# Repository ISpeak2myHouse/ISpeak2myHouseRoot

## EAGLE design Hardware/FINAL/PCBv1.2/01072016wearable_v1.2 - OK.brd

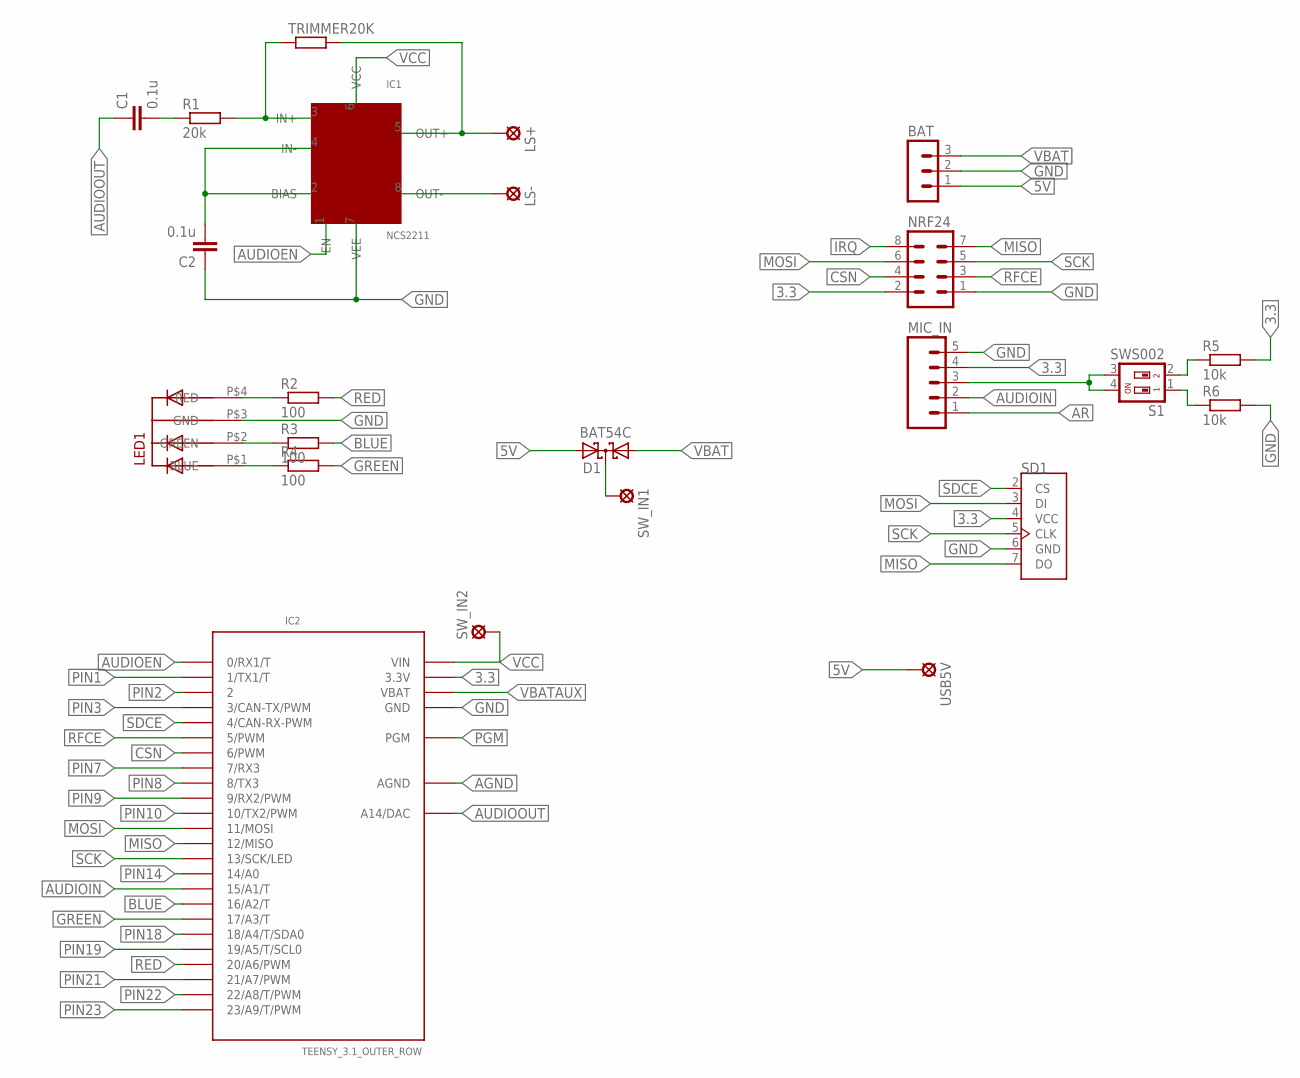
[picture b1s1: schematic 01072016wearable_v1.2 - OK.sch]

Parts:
BAT: MA03-1
C1, C2: 0.1u; C2.5-2
D1: BAT54C; SOT23
IC1: NCS2211; SOIC-8
IC2: TEENSY_3.1_OUTER_ROW; TEENSY3-OUTER_ROW
LED1: 5MMRGBLED; LED5MMRGB
LS+: LSP10
LS-: LSP10
MIC_IN: MA05; 05PA
NRF24: MA04-2
R1: 20k; 0204/7
R2, R3, R4: 100; 0207/2V
R5, R6: 10k; 0207/2V
S1: SWS002; SMS-002
SD1: MICROSD_SF-MICROSD; MICROSD_MICROSD
SW_IN1, SW_IN2: SE11
TRIMMER20K: R-EU_0207/2V; 0207/2V
USB5V: LSP10

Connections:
3.3: IC2.3.3V, IC2.3.3V1 (3.3V), MIC_IN.4, NRF24.2, R5.2, SD1.4 (VCC)
5V: BAT.1, D1.2 (A2), USB5V.MP
AGND: IC2.AGND
AR: MIC_IN.1
AUDIOEN: IC1.1 (EN), IC2.0 (0/RX1/T)
AUDIOIN: IC2.15/A1 (15/A1/T), MIC_IN.2
AUDIOOUT: C1.1, IC2.RESET/DAC (A14/DAC)
BLUE: IC2.16/A2 (16/A2/T), R3.2
CSN: IC2.6 (6/PWM), NRF24.4
GAIN: MIC_IN.3, S1.3, S1.4
GND: BAT.2, C2.1, IC1.7 (VEE), IC2.GND, IC2.GND1 (GND), LED1.P$3 (GND), MIC_IN.5, NRF24.1, R6.2, SD1.6 (GND)
GREEN: IC2.17/A3 (17/A3/T), R4.2
IRQ: NRF24.8
MISO: IC2.12 (12/MISO), NRF24.7, SD1.7 (DO)
MOSI: IC2.11 (11/MOSI), NRF24.6, SD1.3 (DI)
unnamed: D1.3 (CC), SW_IN1.MP
unnamed: IC1.5 (OUT+), LS+.MP, TRIMMER20K.2
unnamed: IC1.3 (IN+), R1.2, TRIMMER20K.1
unnamed: C1.2, R1.1
unnamed: C2.2, IC1.2 (BIAS), IC1.4 (IN-)
unnamed: IC1.8 (OUT-), LS-.MP
unnamed: LED1.P$4 (RED), R2.1
unnamed: LED1.P$1 (BLUE), R4.1
unnamed: LED1.P$2 (GREEN), R3.1
unnamed: R5.1, S1.2
unnamed: R6.1, S1.1
PGM: IC2.PGM
PIN1: IC2.1 (1/TX1/T)
PIN2: IC2.2
PIN3: IC2.3 (3/CAN-TX/PWM)
PIN7: IC2.7 (7/RX3)
PIN8: IC2.8 (8/TX3)
PIN9: IC2.9 (9/RX2/PWM)
PIN10: IC2.10 (10/TX2/PWM)
PIN14: IC2.14/A0
PIN18: IC2.18/A4 (18/A4/T/SDA0)
PIN19: IC2.19/A5 (19/A5/T/SCL0)
PIN21: IC2.21/A7 (21/A7/PWM)
PIN22: IC2.22/A8 (22/A8/T/PWM)
PIN23: IC2.23/A9 (23/A9/T/PWM)
RED: IC2.20/A6 (20/A6/PWM), R2.2
RFCE: IC2.5 (5/PWM), NRF24.3
SCK: IC2.13 (13/SCK/LED), NRF24.5, SD1.5 (CLK)
SDCE: IC2.4 (4/CAN-RX-PWM), SD1.2 (CS)
VBAT: BAT.3, D1.1 (A1)
VBATAUX: IC2.VBAT
VCC: IC1.6 (VCC), IC2.VIN, SW_IN2.MP

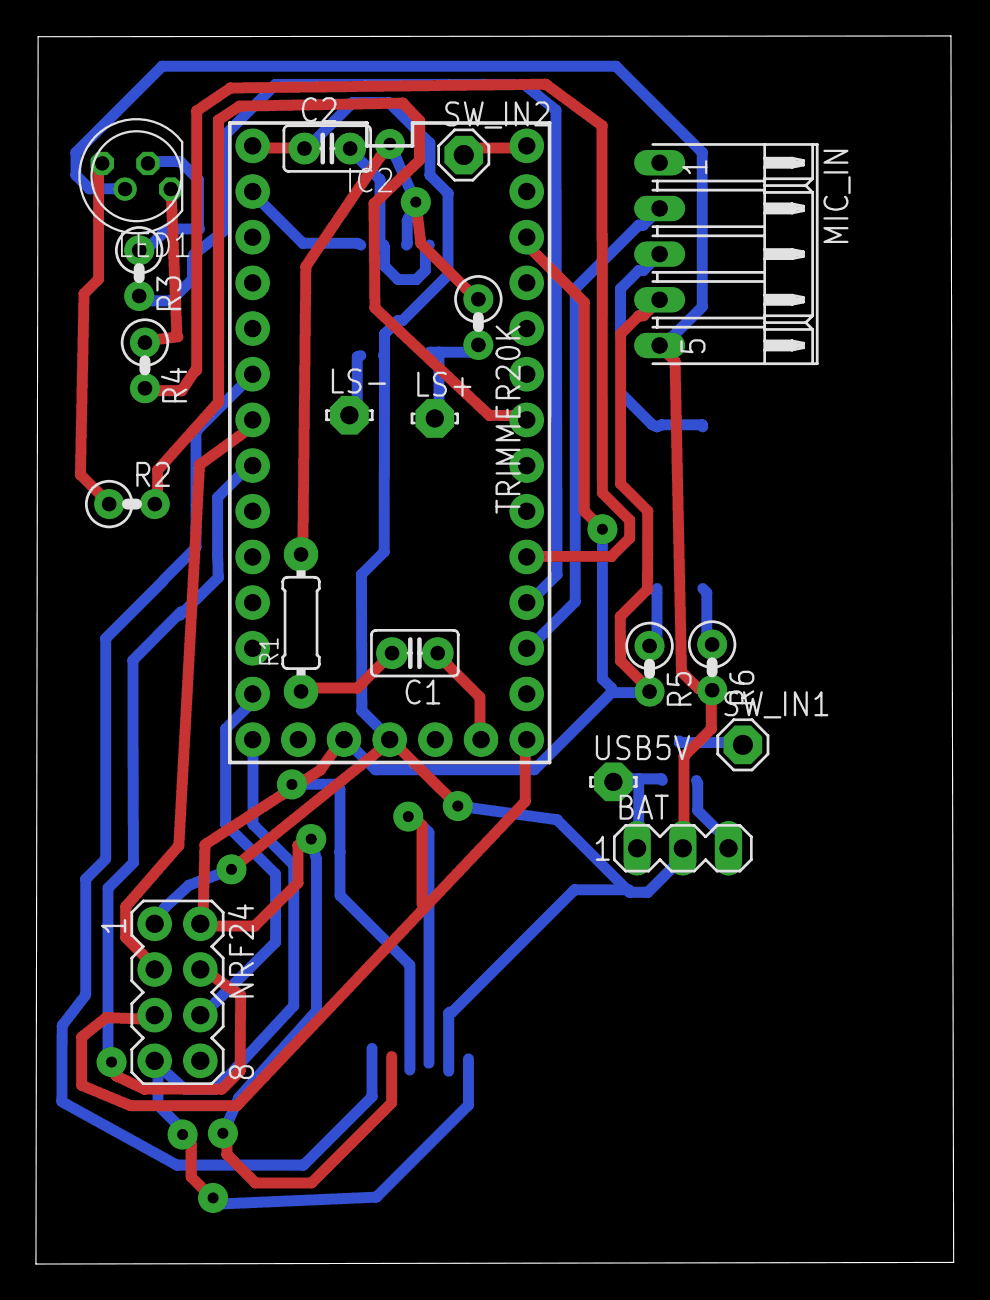
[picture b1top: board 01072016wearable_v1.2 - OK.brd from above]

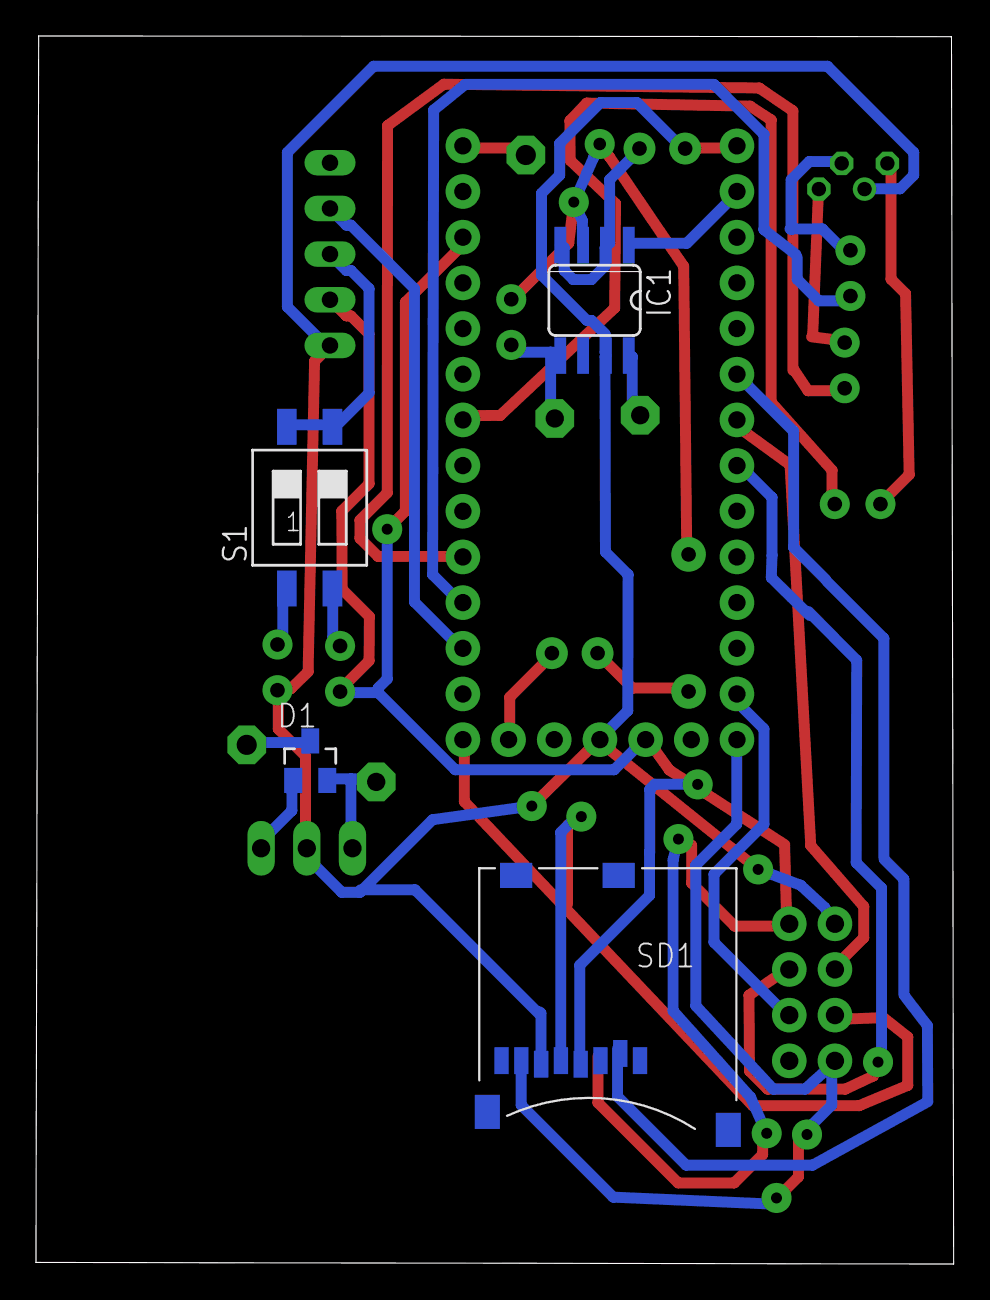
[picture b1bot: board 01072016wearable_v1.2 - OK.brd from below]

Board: 2 copper layers, 51.0 x 68.3 mm, 23 parts (4 on the bottom side), 29 nets.

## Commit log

2016-06-05 latest code
2016-06-06 Code detects touch with a debounce and works only for the GREENLED case
2016-06-07 GIT Tutorial
2016-06-08 new logit written for all the touch cases with switch
2016-06-08 code with new logic for touch
    error... touch reading values have decreased
2016-06-08 working for 1 case
2016-06-08 working but for the negative cases
2016-06-08 going into all the case loops but switching back before action could be executed
2016-06-08 works fine for one loop
2016-06-08 works for green with new code
2016-06-08 Source code for sender with all working cases
2016-06-08 Touch with all cases working
2016-06-09 Folder for all software
2016-06-09 Removed code to Software folder
2016-06-09 Removed Code directory and moved it to software
2016-07-15 Add files via upload
    The Receiver Code for our project :)
2016-08-07 hardware updated
2016-08-07 final code
2016-08-07 unzipped
2016-08-11 The final Mechanical Design
